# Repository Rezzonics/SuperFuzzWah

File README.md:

# SuperFuzzWah (Eagle 6.3.0)
Super Fuzz Wah guitar pedal (based on Shin-Ei Fuzz Wah / Univox SuperFuzz) Not a clone!!:

- Simulation (LTSpice Simulation Files)
  => GyratorWah 
  => SuperFuzzWah
- Eagle CAD files:
  => Schematics and BoM
  => PCB
  => Gerbers

Main features
- Germanium diodes replaced by Schottky diodes
- Inductor replaced by Gyrator circuit
- 9V DC voltage doubler ICL7660S

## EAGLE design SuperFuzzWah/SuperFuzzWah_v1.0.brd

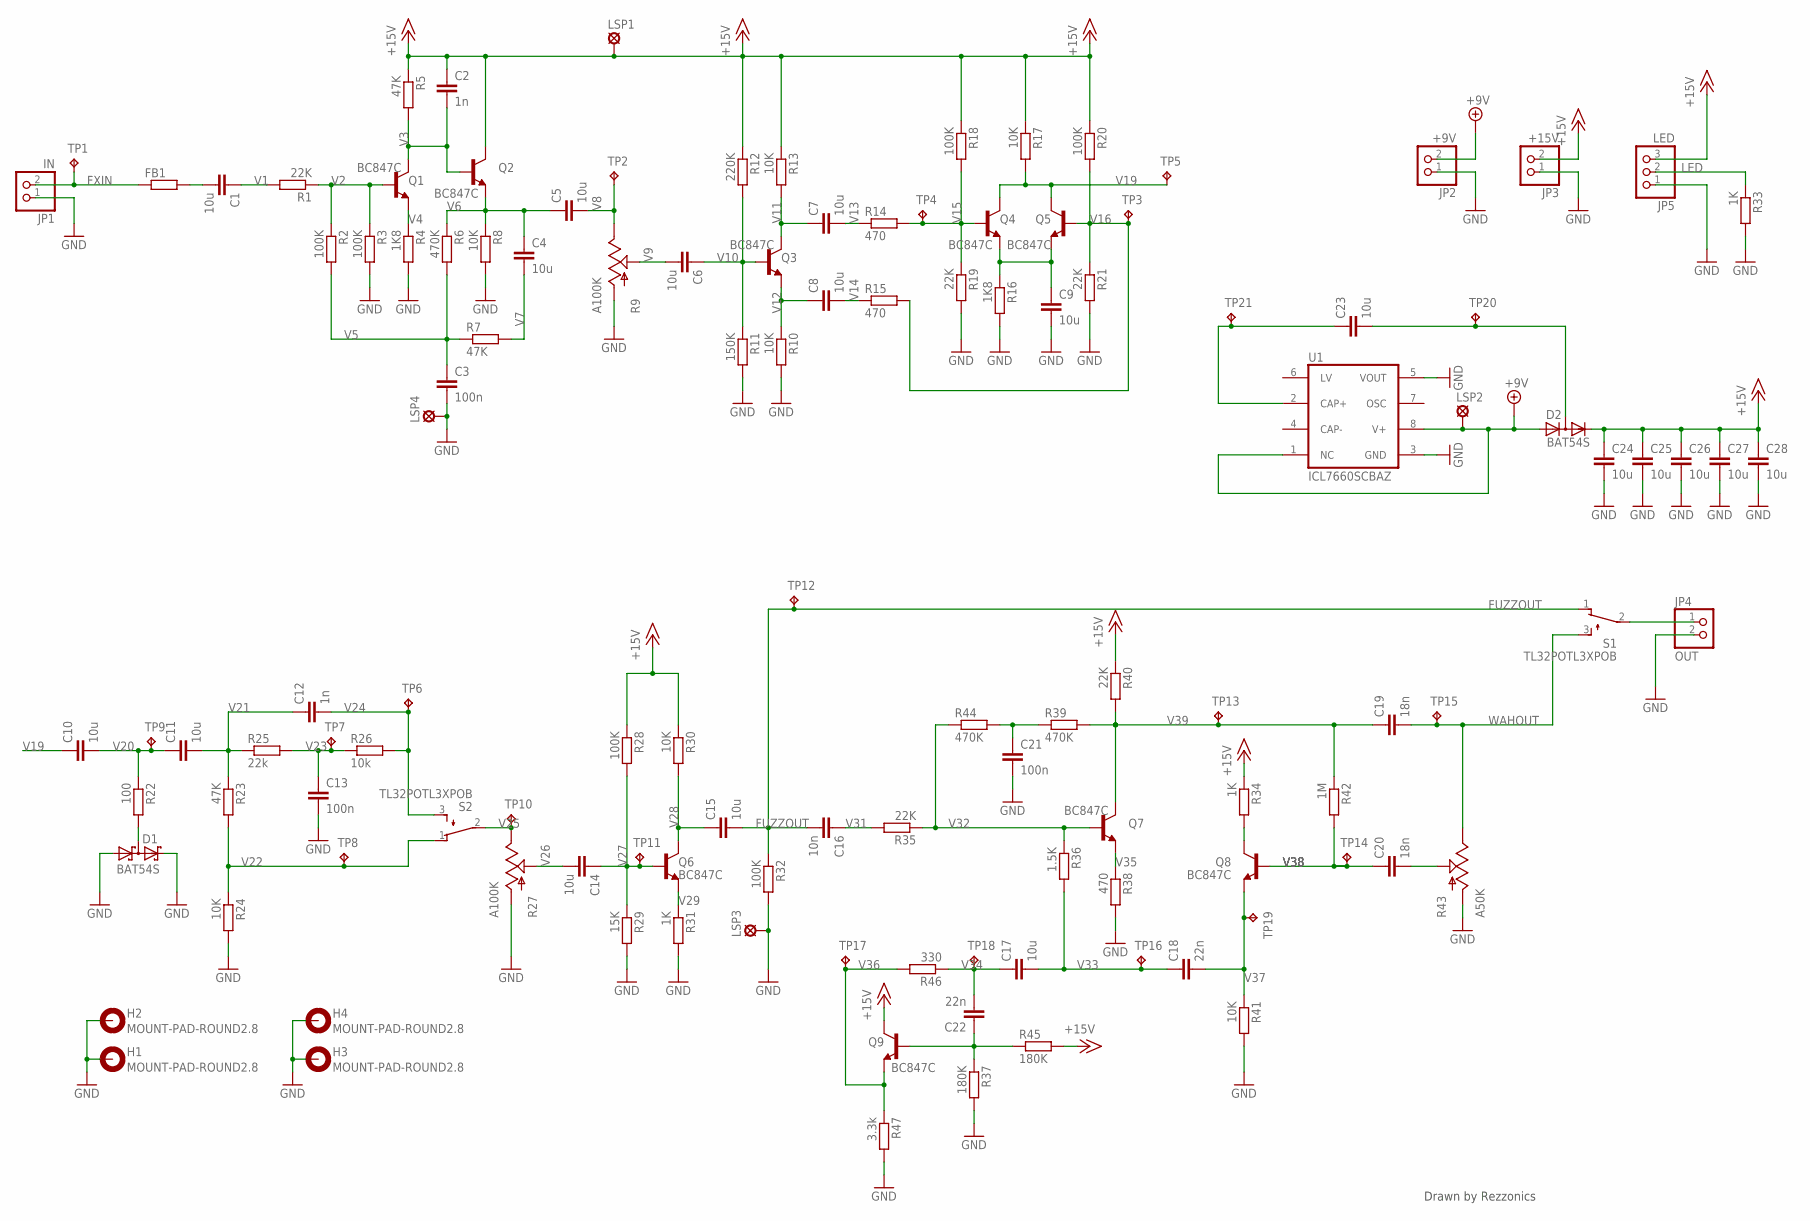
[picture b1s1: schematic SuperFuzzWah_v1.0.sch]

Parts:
C1, C4, C5, C6, C7, C8, C9, C10, C11, C14, C15, C17, C23, C24, C25, C26, C27, C28: 10u; C0805K; MPN GRM21BR61E106KA73L
C2, C12: 1n; C0805K; MPN GRM1885C1H102FA01D
C3, C13, C21: 100n; C1210K; MPN CB027D0104JBA
C16: 10n; C0603K; MPN ESD35C103K4T2A-18
C18, C22: 22n; C1210K; MPN ECH-U1H223JX5
C19, C20: 18n; C1210K; MPN ECH-U1H183GX5
D1, D2: BAT54S; SOT23; MPN BAT54S
FB1: R-EU_R1206; R1206; MPN BLM31PG121SN1L
H1, H2, H3, H4: MOUNT-PAD-ROUND2.8; 2,8-PAD; MPN *
JP1: IN; 1X02; MPN 77311-401-36LF
JP2: +9V; 1X02; MPN 77311-401-36LF
JP3: +15V; 1X02; MPN 77311-401-36LF
JP4: OUT; 1X02; MPN 77311-401-36LF
JP5: LED; 1X03; MPN 77311-401-36LF
LSP1, LSP2, LSP3, LSP4: LSP13; MPN 1249
Q1, Q2, Q3, Q4, Q5, Q6, Q7, Q8, Q9: BC847C; SOT23-BEC; MPN BC847C,215
R1, R19, R21, R35, R40: 22K; R0603; MPN ERJ-3EKF2202V
R2, R3, R18, R20, R28, R32: 100K; R0603; MPN CR0603-FX-1003ELF
R4, R16: 1K8; R0603; MPN ERJ-3EKF1801V
R5, R7, R23: 47K; R0603; MPN RK73H1JTTD4702F
R6, R39, R44: 470K; R0603; MPN ERJ-3EKF4703V
R8, R10, R13, R17, R24, R30, R41: 10K; R0603; MPN CR0603-FX-1002HLF
R9, R27: A100K; POT_ALPHA_RV16AF-20; MPN RV16AF-10-20R1-A100K
R11: 150K; R0603; MPN CRCW0603150KFKEB
R12: 220K; R0603; MPN ERJ-3EKF2203V
R14, R15, R38: 470; R0603; MPN CR0603-FX-4700ELF
R22: 100; R0603; MPN CR0201-FW-1000GLF
R25: 22k; R0603; MPN ERJ-3EKF2202V
R26: 10k; R0603; MPN CR0603-FX-1002HLF
R29: 15K; R0603; MPN RK73H1HTTC1502F
R31, R33, R34: 1K; R0603; MPN CR0603-FX-1001HLF
R36: 1.5K; R0603; MPN ERJ-3EKF1501V
R37, R45: 180K; R0603; MPN CR0603-FX-1803ELF
R42: 1M; R0603; MPN CR0603-FX-1004ELF
R43: A50K; POT_ALPHA_RV16AF-20; MPN RV16AF-10-20R1-A50K
R46: 330; R0603; MPN ERJ-3EKF3300V
R47: 3.3k; R0603; MPN RK73H1JTTDD3321F
S1, S2: TL32POTL3XPOB; TL3XPOB; MPN M2012SS1W01
TP1, TP2, TP3, TP4, TP5, TP6, TP7, TP8, TP9, TP10, TP11, TP12, TP13, TP14, TP15, TP16, TP17, TP18, TP19, TP20, TP21: TPTP10R; TP10R; MPN *
U1: ICL7660SCBAZ; SO08; MPN ICL7660SCBAZ

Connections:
+9V: D2.1 (A), JP2.2, LSP2.MP, U1.1 (NC), U1.8 (V+)
+15V: C2.1, C24.1, C25.1, C26.1, C27.1, C28.1, D2.2 (C), JP3.2, JP5.3, LSP1.MP, Q2.C, Q9.C, R5.1, R12.1, R13.1, R17.1, R18.1, R20.1, R28.1, R30.1, R34.1, R40.1, R45.2
FUZZOUT: C15.2, C16.2, R32.1, S1.1 (O), TP12.TP
FXIN: FB1.1, JP1.2, TP1.TP
GND: C3.2, C9.2, C13.2, C21.2, C24.2, C25.2, C26.2, C27.2, C28.2, D1.1 (A1), D1.2 (C2), H1.B2,8, H2.B2,8, H3.B2,8, H4.B2,8, JP1.1, JP2.1, JP3.1, JP4.2, JP5.1, LSP3.MP, LSP4.MP, R3.2, R4.2, R8.2, R9.1 (A), R10.2, R11.2, R16.2, R19.2, R21.2, R24.2, R27.1 (A), R29.2, R31.2, R32.2, R33.2, R37.2, R38.2, R41.2, R43.1 (A), R47.2, U1.3 (GND), U1.5 (VOUT)
LED: JP5.2, R33.1
unnamed: D1.3 (C1A2), R22.2
unnamed: C20.2, R43.2 (S)
unnamed: C21.1, R39.1, R44.2
unnamed: Q8.C, R34.2
unnamed: JP4.1, S1.2
unnamed: C22.1, Q9.B, R37.1, R45.1
unnamed: C1.2, FB1.2
unnamed: C23.1, TP21.TP, U1.2 (CAP+)
unnamed: C23.2, D2.3 (AC), TP20.TP
unnamed: C9.1, Q4.E, Q5.E, R16.1
V1: C1.1, R1.2
V2: Q1.B, R1.1, R2.1, R3.1
V3: C2.2, Q1.C, Q2.B, R5.2
V4: Q1.E, R4.1
V5: C3.1, R2.2, R6.2, R7.1
V6: C4.1, C5.1, Q2.E, R6.1, R8.1
V7: C4.2, R7.2
V8: C5.2, R9.3 (E), TP2.TP
V9: C6.2, R9.2 (S)
V10: C6.1, Q3.B, R11.1, R12.2
V11: C7.1, Q3.C, R13.2
V12: C8.1, Q3.E, R10.1
V13: C7.2, R14.1
V14: C8.2, R15.1
V15: Q4.B, R14.2, R18.2, R19.1, TP4.TP
V16: Q5.B, R15.2, R20.2, R21.1, TP3.TP
V19: C10.1, Q4.C, Q5.C, R17.2, TP5.TP
V20: C10.2, C11.1, R22.1, TP9.TP
V21: C11.2, C12.1, R23.1, R25.1
V22: R23.2, R24.1, S2.1 (O), TP8.TP
V23: C13.1, R25.2, R26.1, TP7.TP
V24: C12.2, R26.2, S2.3 (S), TP6.TP
V25: R27.3 (E), S2.2, TP10.TP
V26: C14.2, R27.2 (S)
V27: C14.1, Q6.B, R28.2, R29.1, TP11.TP
V28: C15.1, Q6.C, R30.2
V29: Q6.E, R31.1
V31: C16.1, R35.2
V32: Q7.B, R35.1, R36.1, R44.1
V33: C17.2, C18.1, R36.2, TP16.TP
V34: C17.1, C22.2, R46.1, TP18.TP
V35: Q7.E, R38.1
V36: Q9.E, R46.2, R47.1, TP17.TP
V37: C18.2, Q8.E, R41.1, TP19.TP
V38: C20.1, Q8.B, R42.2, TP14.TP
V39: C19.1, Q7.C, R39.2, R40.2, R42.1, TP13.TP
WAHOUT: C19.2, R43.3 (E), S1.3 (S), TP15.TP

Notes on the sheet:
Drawn by Rezzonics

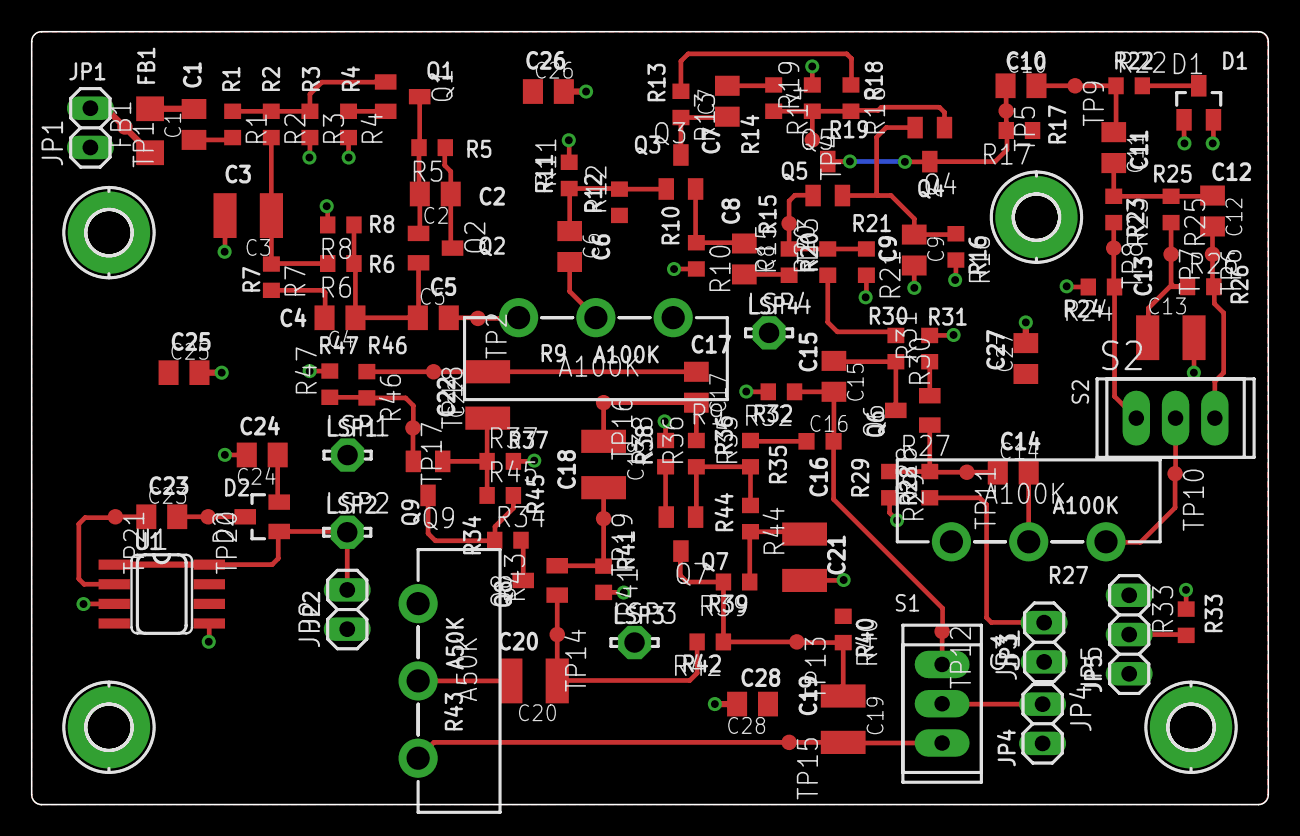
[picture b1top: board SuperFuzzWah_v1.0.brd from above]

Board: 2 copper layers, 80.0 x 50.0 mm, 124 parts (0 on the bottom side), 53 nets.

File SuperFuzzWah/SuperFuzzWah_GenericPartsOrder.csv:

Mfg Part Num,Mfg Name,VID,Vendor Part Num,Description,Customer Ref,Qty-1,Qty-5,Qty-25,Part References,Value
BLM31PG121SN1L,Murata,ME,81-BLM31PG121SN1L,EMI Filter Beads, Chokes & Arrays 1206 120 OHM,emi001,1,5,25,"FB1",
77311-401-36LF,FCI,ME,649-77311-401-36LF,Headers & Wire Housings 36P STR SR TMT HDR TIN .425IN LENGTH,con007,1,5,25,"JP2",+9V
77311-401-36LF,FCI,ME,649-77311-401-36LF,Headers & Wire Housings 36P STR SR TMT HDR TIN .425IN LENGTH,con007,1,5,25,"JP3",+15V
ERJ-3EKF1501V,Panasonic,ME,667-ERJ-3EKF1501V,Thick Film Resistors - SMD 0603 1.5Kohms 1% Tol,res055,1,5,25,"R36",1.5K
CR0603-FX-1001HLF,Bourns,ME,652-CR0603-FX1001HLF,Thick Film Resistors - SMD 1KOHM 1/10WATT 1%,res001,3,15,75,"R31, R33, R34",1K
ERJ-3EKF1801V,Panasonic,ME,667-ERJ-3EKF1801V,Thick Film Resistors - SMD 0603 1.8Kohms 1% Tol,res020,2,10,50,"R4, R16",1K8
CR0603-FX-1004ELF,Bourns,ME,652-CR0603FX-1004ELF,Thick Film Resistors - SMD 1M 1% 1/10W,res003,1,5,25,"R42",1M
GRM1885C1H102FA01D,Murata,ME,81-GRM1885C1H102FA1D,Multilayer Ceramic Capacitors MLCC - SMD/SMT 1000PF 50V 1%,capcer017,2,10,50,"C2, C12",1n
RK73H1JTTDD3321F,KOA Speer,ME,660-RK73H1JTTDD3321F,Thick Film Resistors - SMD 1/10watts 3.32Kohms,res016,1,5,25,"R47",3.3k
CR0603-FX-1002HLF,Bourns,ME,652-CR0603-FX1002HLF,Thick Film Resistors - SMD 10KOHM 1/10WATT 1%,res002,7,35,175,"R8, R10, R13, R17, R24, R30, R41",10K
CR0603-FX-1002HLF,Bourns,ME,652-CR0603-FX1002HLF,Thick Film Resistors - SMD 10KOHM 1/10WATT 1%,res002,1,5,25,"R26",10k
ESD35C103K4T2A-18,AVX,ME,581-ESD35C103K4T2A18,Multilayer Ceramic Capacitors MLCC - SMD/SMT 50volts 0.01uF 10% X7R 0603 SIZE,capcer029,1,5,25,"C16",10n
GRM21BR61E106KA73L,Murata,ME,81-GRM21BR61E106KA3L,Multilayer Ceramic Capacitors MLCC - SMD/SMT 0805 X5R 25V 10uF,capcer020,18,90,450,"C1, C4, C5, C6, C7, C8, C9, C10, C11, C14, C15, C17, C23, C24, C25, C26, C27, C28",10u
RK73H1HTTC1502F,KOA Speer,ME,660-RK73H1HTTC1502F,Thick Film Resistors - SMD 15K OHM 1%,res025,1,5,25,"R29",15K
ECH-U1H183GX5,Panasonic,ME,667-ECH-U1H183GX5,Film Capacitors 0.018uF 50volts 2% 1210 PPS Film,capfilm015,2,10,50,"C19, C20",18n
ERJ-3EKF2202V,Panasonic,ME,667-ERJ-3EKF2202V,Thick Film Resistors - SMD 0603 22Kohms 1% Tol,res056,5,25,125,"R1, R19, R21, R35, R40",22K
ERJ-3EKF2202V,Panasonic,ME,667-ERJ-3EKF2202V,Thick Film Resistors - SMD 0603 22Kohms 1% Tol,res056,1,5,25,"R25",22k
ECH-U1H223JX5,Panasonic,ME,667-ECH-U1H223JX5,Film Capacitors 0.022uF 50volts 5% 1210 PPS Film,capfilm014,2,10,50,"C18, C22",22n
RK73H1JTTD4702F,KOA Speer,ME,660-RK73H1JTTD4702F,Thick Film Resistors - SMD 1/10watts 47Kohms 1%,res040,3,15,75,"R5, R7, R23",47K
CR0201-FW-1000GLF,Bourns,ME,652-CR0201FW-1000GLF,Thick Film Resistors - SMD 100ohm 1% 250ppm,res014,1,5,25,"R22",100
CR0603-FX-1003ELF,Bourns,ME,652-CR0603-FX-103ELF,Thick Film Resistors - SMD 100K 1% 1/10 WATT,res004,6,30,150,"R2, R3, R18, R20, R28, R32",100K
CB027D0104JBA,AVX,ME,581-CB027D0104J,Film Capacitors 50vOLT 0.1uF 5% 1210,capfilm002,3,15,75,"C3, C13, C21",100n
CRCW0603150KFKEB,Vishay,ME,71-CRCW0603150KFKEB,Thick Film Resistors - SMD 1/10watt 150Kohms 1%,res049,1,5,25,"R11",150K
CR0603-FX-1803ELF,Bourns,ME,652-CR0603FX-1803ELF,Thick Film Resistors - SMD 180K 1% 1/10W,res006,2,10,50,"R37, R45",180K
ERJ-3EKF2203V,Panasonic,ME,667-ERJ-3EKF2203V,Thick Film Resistors - SMD 0603 220Kohms 1% Tol,res057,1,5,25,"R12",220K
ERJ-3EKF3300V,Panasonic,ME,667-ERJ-3EKF3300V,Thick Film Resistors - SMD 0603 330ohms 1% Tol,res058,1,5,25,"R46",330
CR0603-FX-4700ELF,Bourns,ME,652-CR0603FX-4700ELF,Thick Film Resistors - SMD 470 ohm 1%,res011,3,15,75,"R14, R15, R38",470
ERJ-3EKF4703V,Panasonic,ME,667-ERJ-3EKF4703V,Thick Film Resistors - SMD 0603 470Kohms 1% Tol,res051,3,15,75,"R6, R39, R44",470K
RV16AF-10-20R1-A50K,Alpha (Taiwan),ME,31JA405-F,Potentiometers Audio 50K Solder Lugs,pot007,1,5,25,"R43",A50K
RV16AF-10-20R1-A100K,Alpha (Taiwan),ME,31JA501-F,Potentiometers Audio 100K Solder Lugs,pot008,2,10,50,"R9, R27",A100K
BAT54S,Fairchild Semiconductor,ME,512-BAT54S,Schottky Diodes & Rectifiers 30V 200mA,diodes004,1,5,25,"D1",BAT54S
BAT54S,Fairchild Semiconductor,ME,512-BAT54S,Schottky Diodes & Rectifiers 30V 200mA,diodes004,1,5,25,"D2",BAT54S
BC847C,215,NXP,ME,771-BC847C-T/R,Transistors Bipolar - BJT NPN GP 100MA 45V,bjt004,9,45,225,"Q1, Q2, Q3, Q4, Q5, Q6, Q7, Q8, Q9",BC847C
ICL7660CBAZ,Intersil,ME,968-ICL7660CBAZ,Voltage Regulators - Switching Regulators CMOS VOLT CONVERTER 8 COM,icreg004,1,5,25,"U1",ICL7660CSA
77311-401-36LF,FCI,ME,649-77311-401-36LF,Headers & Wire Housings 36P STR SR TMT HDR TIN .425IN LENGTH,con007,1,5,25,"JP1",IN
77311-401-36LF,FCI,ME,649-77311-401-36LF,Headers & Wire Housings 36P STR SR TMT HDR TIN .425IN LENGTH,con007,1,5,25,"JP5",LED
1249,Keystone electronics,ME,534-1249,Test Points TP TERM BRS MATTE TINNED PLATED,tp001,4,20,100,"LSP1, LSP2, LSP3, LSP4",LSP13
*** ERROR - PART '*' NOT FOUND FOR: "H1, H2, H3, H4"
77311-401-36LF,FCI,ME,649-77311-401-36LF,Headers & Wire Housings 36P STR SR TMT HDR TIN .425IN LENGTH,con007,1,5,25,"JP4",OUT
M2012SS1W01,NKK Switches,ME,633-M201201,Toggle Switches ON-NONE-ON SPDT,sw005,2,10,50,"S1, S2",TL32POTL3XPOB
*** ERROR - PART '*' NOT FOUND FOR: "TP1, TP2, TP3, TP4, TP5, TP6, TP7, TP8, TP9, TP10, TP11, TP12, TP13, TP14, TP15, TP16, TP17, TP18, TP19, TP20, TP21"

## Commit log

2015-08-23 Rezzonics version of the Shin-Ei Fuzz-Wah (not a clone!) - Schematics, PCB layout, simulations http://rezzonics.blogspot.fr/2014/11/rezzonics-version-of-shin-ei-fuzz-wah.html

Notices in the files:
parts and their libraries:
SparkFun: Licensing: CC v3.0 Share-Alike You are welcome to use this library for commercial purposes.
